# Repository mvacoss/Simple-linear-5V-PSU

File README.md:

# Simple-linear-5V-PSU
- Simple linear PSU design with LM7805
- Without watermark, without useless names
- It is double sided, but you can also export only single sided layout (B_Cu), so it is ideal for DIY etching
- I included already exported PDF of the [B_Cu](https://github.com/user-attachments/files/26326793/Etch.pdf) too, so you don't have to open KiCad at all! But remember, the side with the ink on it goes directly to the copper layer of your PCB

## Specs
- ~6V - ~10V IN
- +5V OUT
- MAX 1A (with suitable heatsink)
- Onboard LED indication (Lights up when the output is +5V)

## BOM

## Dimensions
39.75 mm (approximately 1.565 in) by 16.75 mm (approximately 0.66 in)

**Board layout preview**

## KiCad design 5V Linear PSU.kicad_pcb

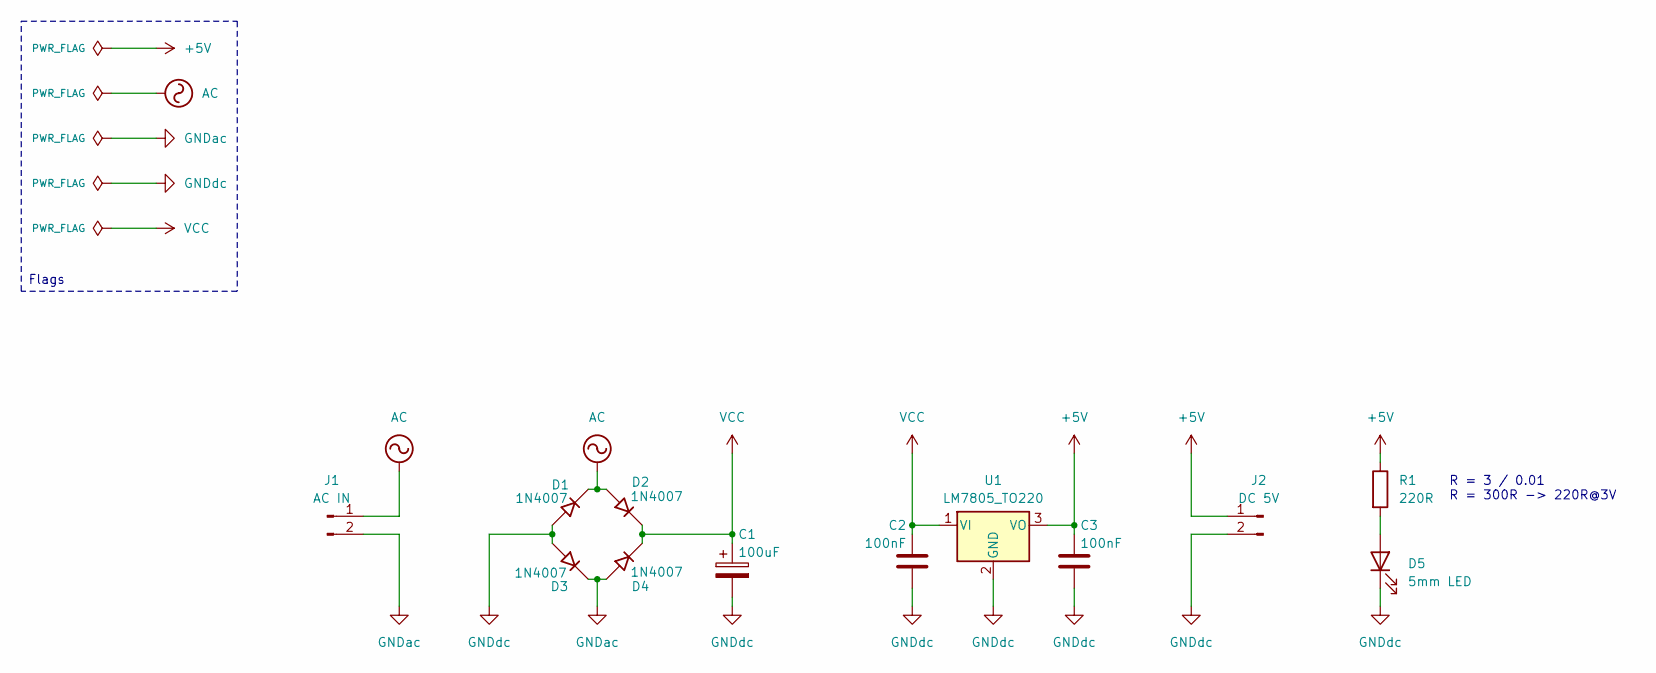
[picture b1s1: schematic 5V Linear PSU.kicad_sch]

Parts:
C1: 100uF; CP_Radial_D6.3mm_P2.50mm
C2, C3: 100nF; C_Disc_D7.0mm_W2.5mm_P5.00mm
D1, D2, D3, D4: 1N4007; D_DO-41_SOD81_P10.16mm_Horizontal
D5: 5mm LED; LED_D5.0mm
J1: AC IN; PinHeader_1x02_P2.54mm_Vertical
J2: DC 5V; PinHeader_1x02_P2.54mm_Vertical
R1: 220R; R_Axial_DIN0207_L6.3mm_D2.5mm_P10.16mm_Horizontal
U1: LM7805_TO220; TO-220-3_Vertical

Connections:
+5V: C3.1, J2.1, R1.1, U1.3 (VO)
AC: D1.1 (K), D2.2 (A), J1.1
GNDac: D3.1 (K), D4.2 (A), J1.2
GNDdc: C1.2, C2.2, C3.2, D1.2 (A), D3.2 (A), D5.1 (K), J2.2, U1.2 (GND)
unnamed: D5.2 (A), R1.2
VCC: C1.1, C2.1, D2.1 (K), D4.1 (K), U1.1 (VI)

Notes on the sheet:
R = 3 / 0.01 R = 300R -> 220R@3V
Flags

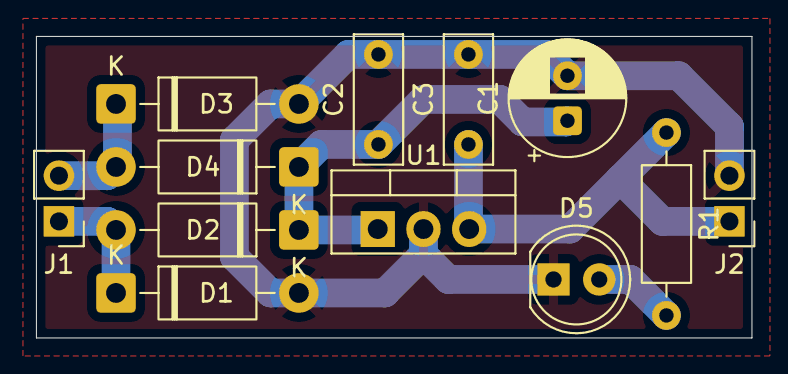
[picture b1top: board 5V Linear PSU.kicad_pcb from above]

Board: 2 copper layers, 39.8 x 16.8 mm, 12 parts (0 on the bottom side), 6 nets.

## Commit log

2026-02-08 added kicad files
2026-03-28 A few more touches to the readme
